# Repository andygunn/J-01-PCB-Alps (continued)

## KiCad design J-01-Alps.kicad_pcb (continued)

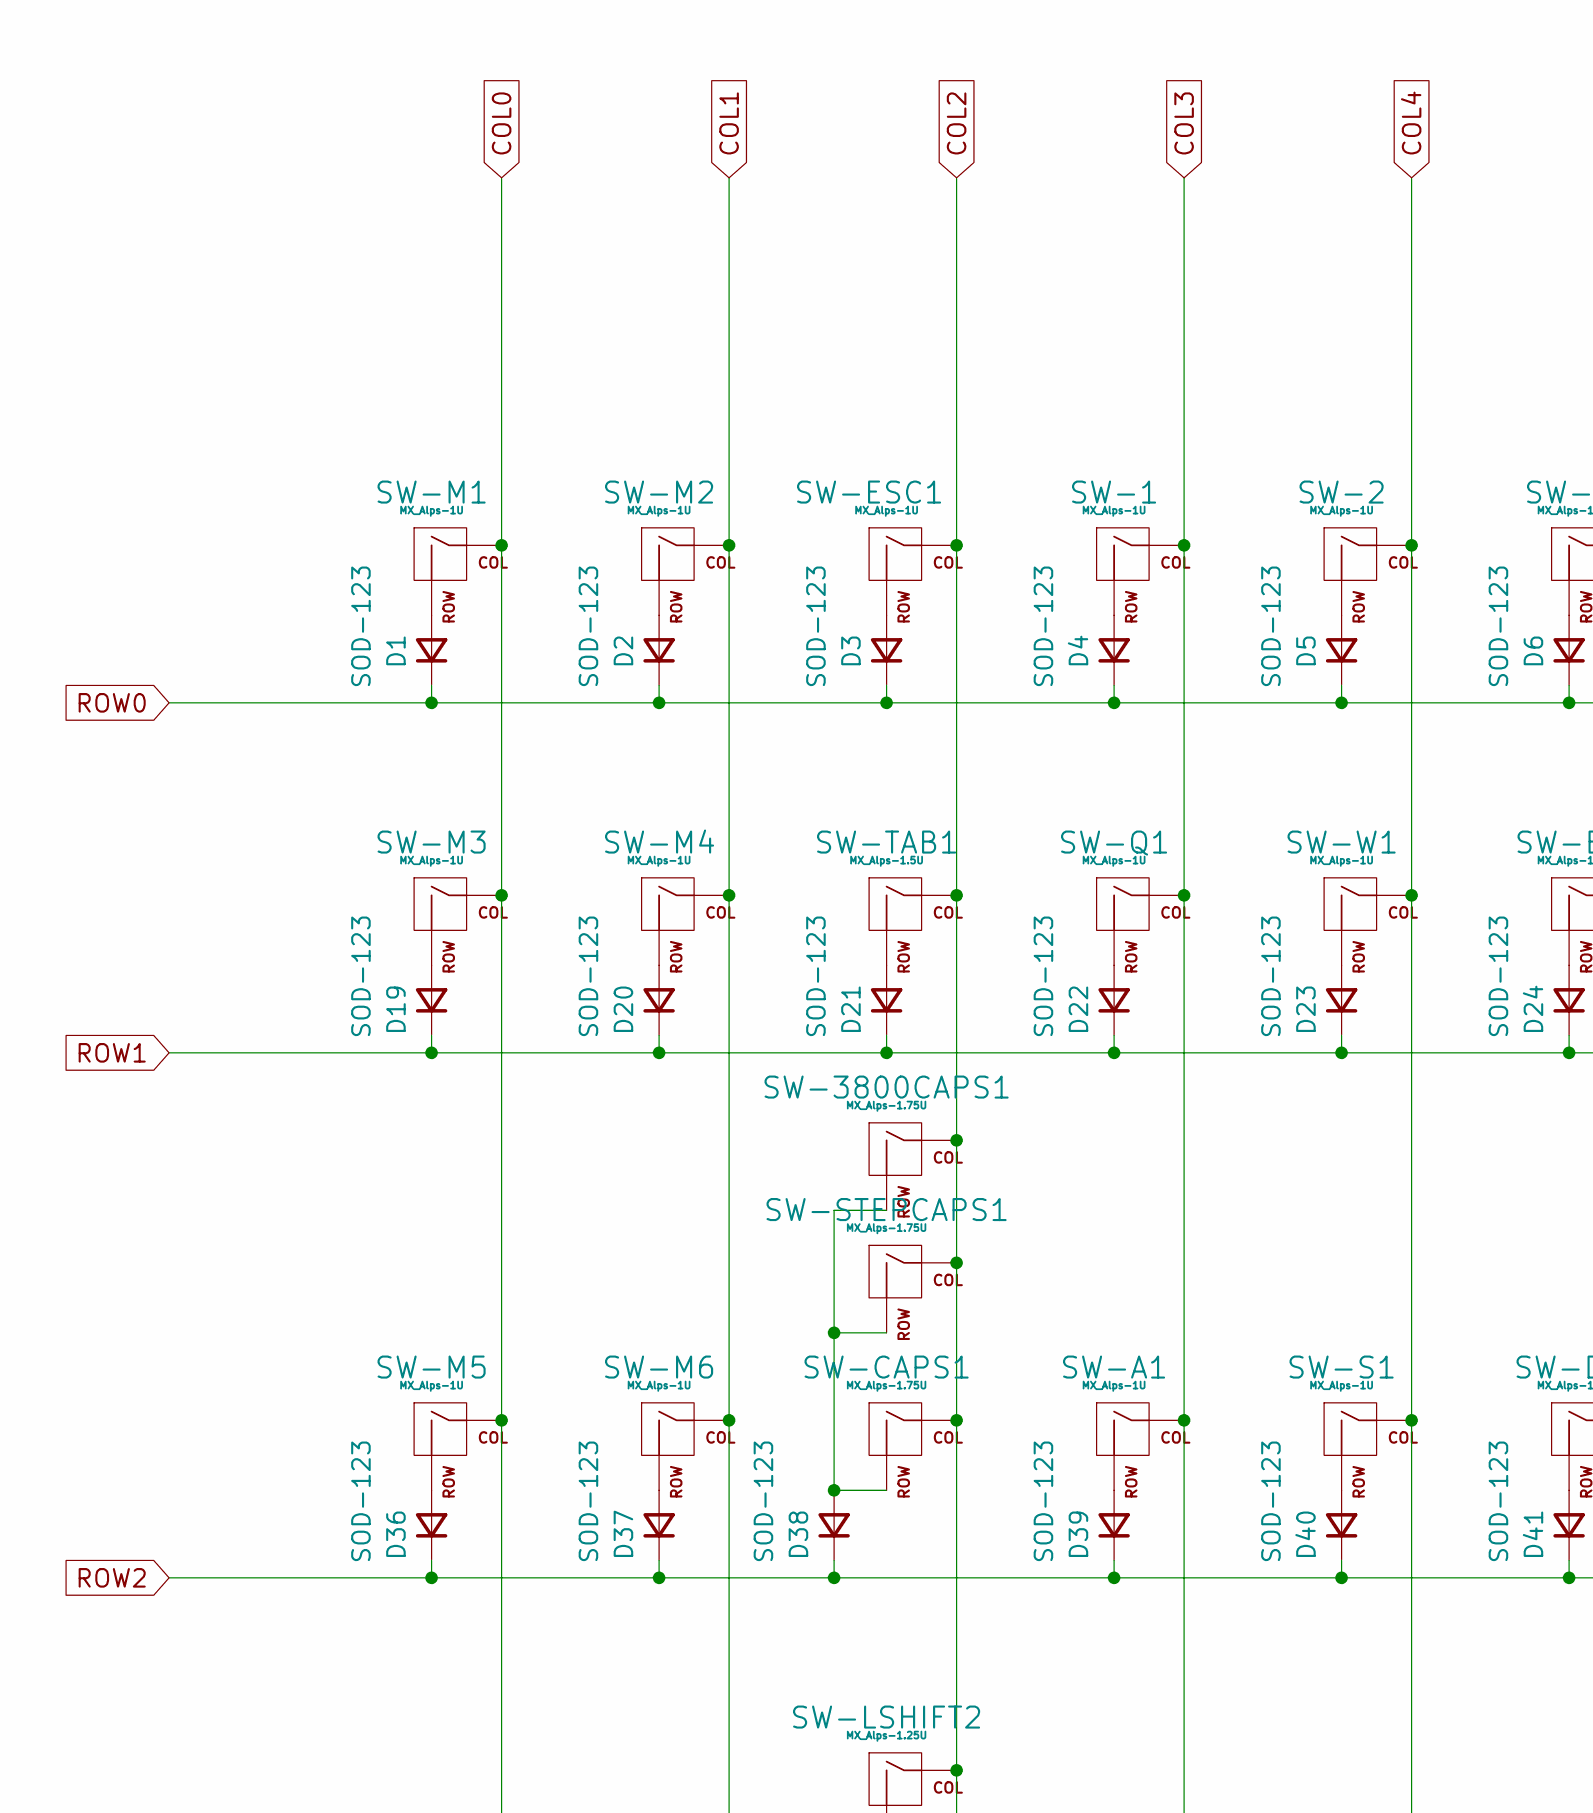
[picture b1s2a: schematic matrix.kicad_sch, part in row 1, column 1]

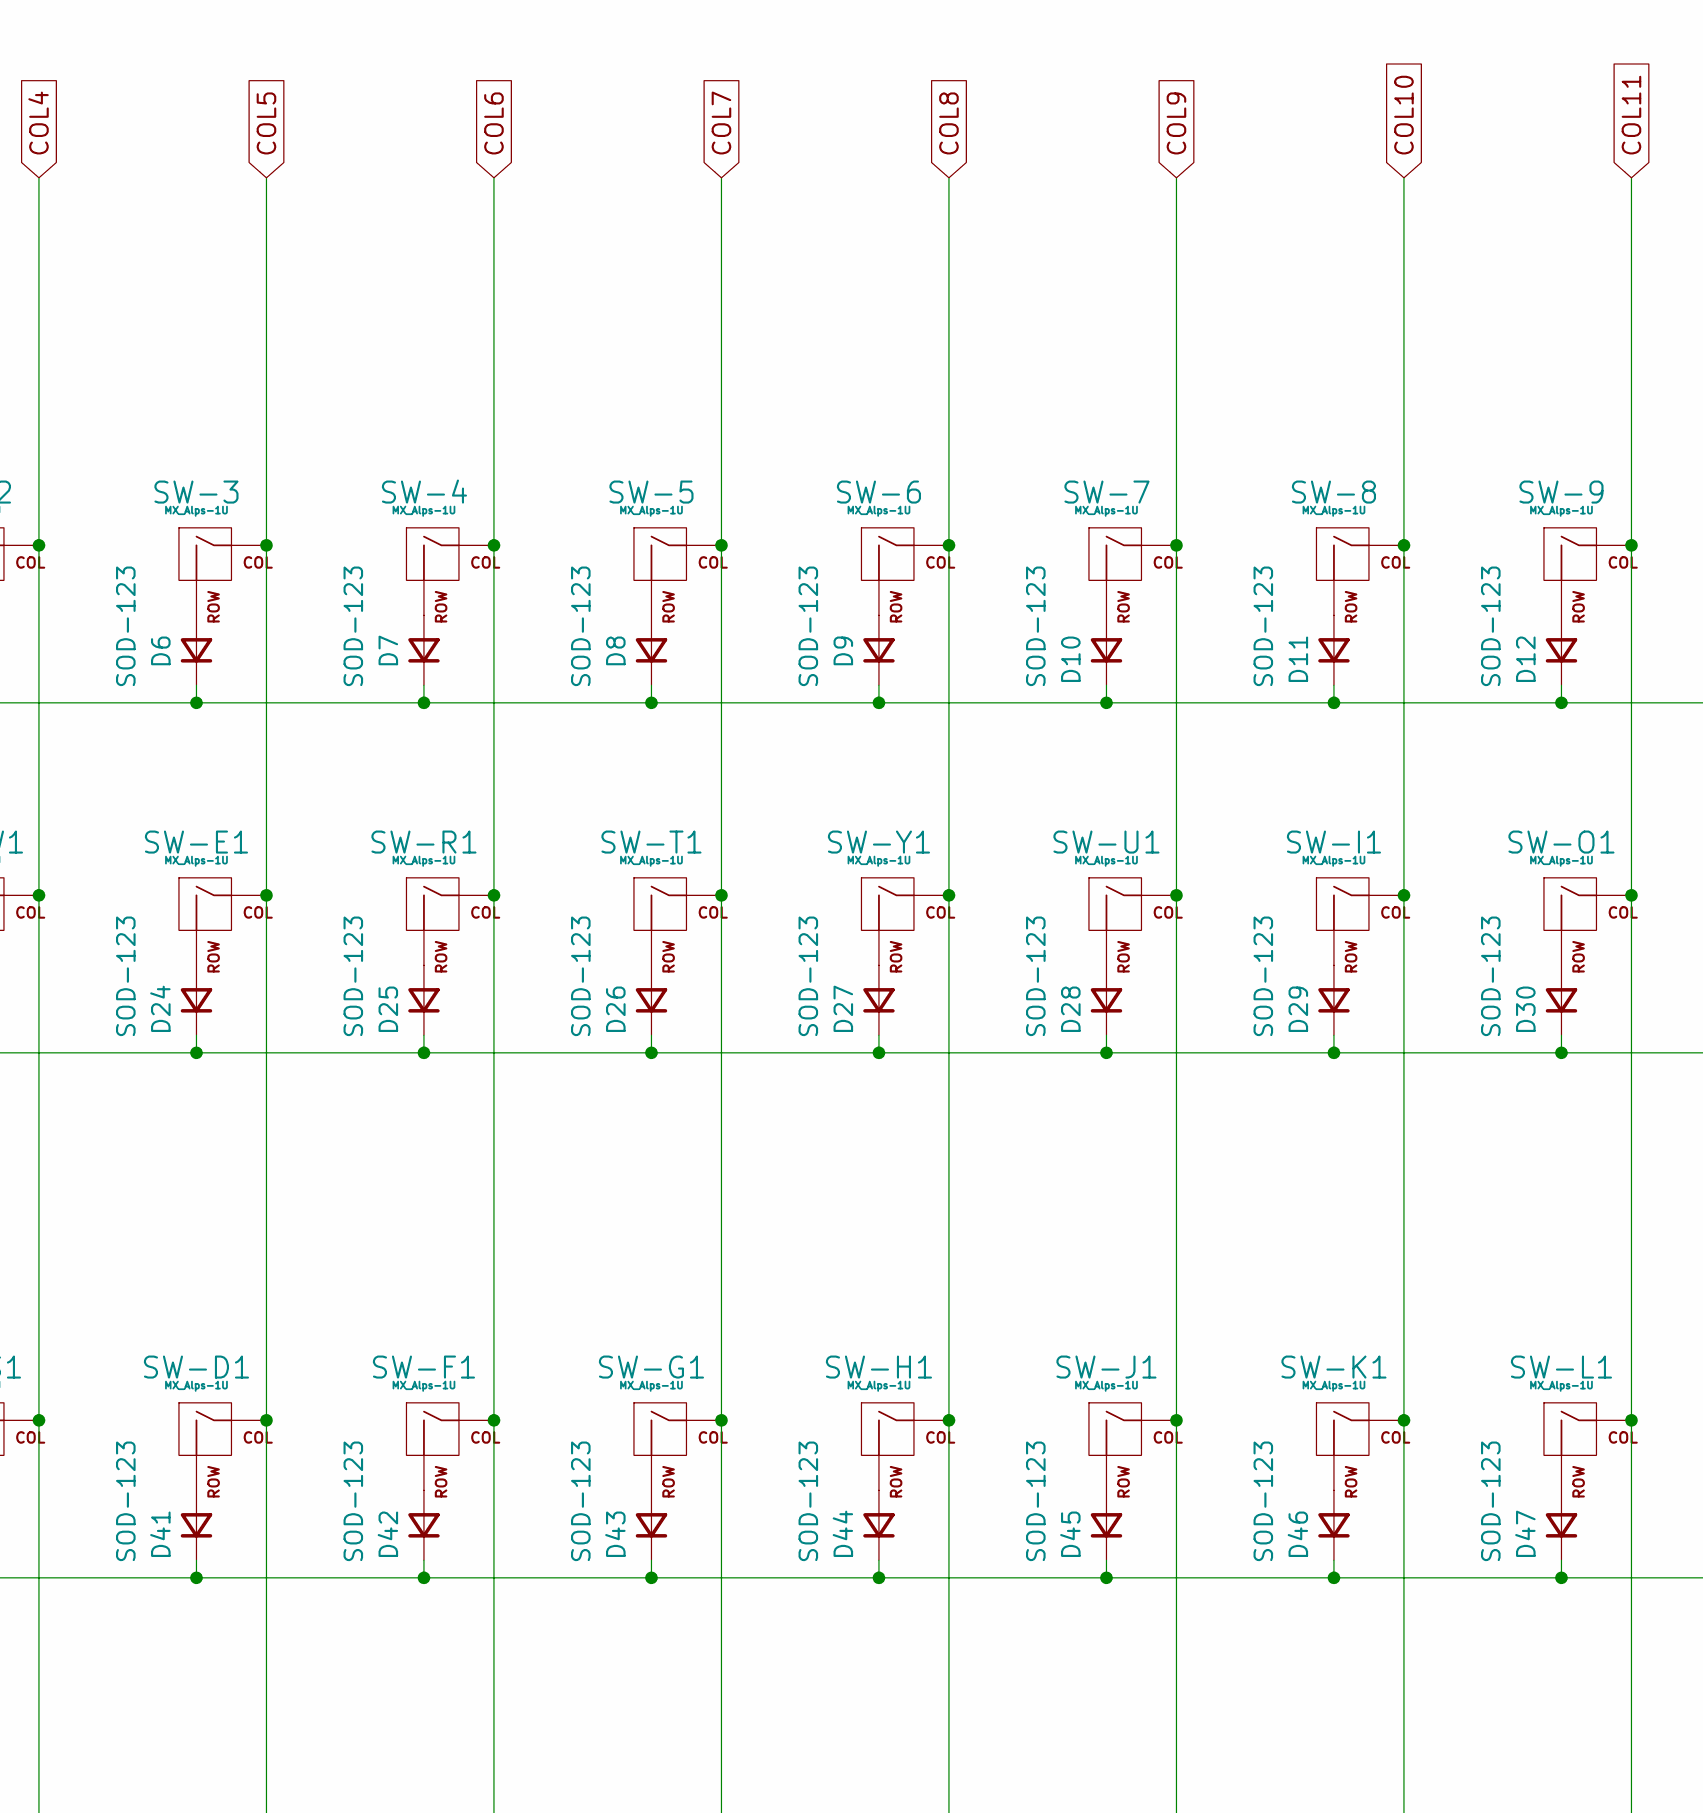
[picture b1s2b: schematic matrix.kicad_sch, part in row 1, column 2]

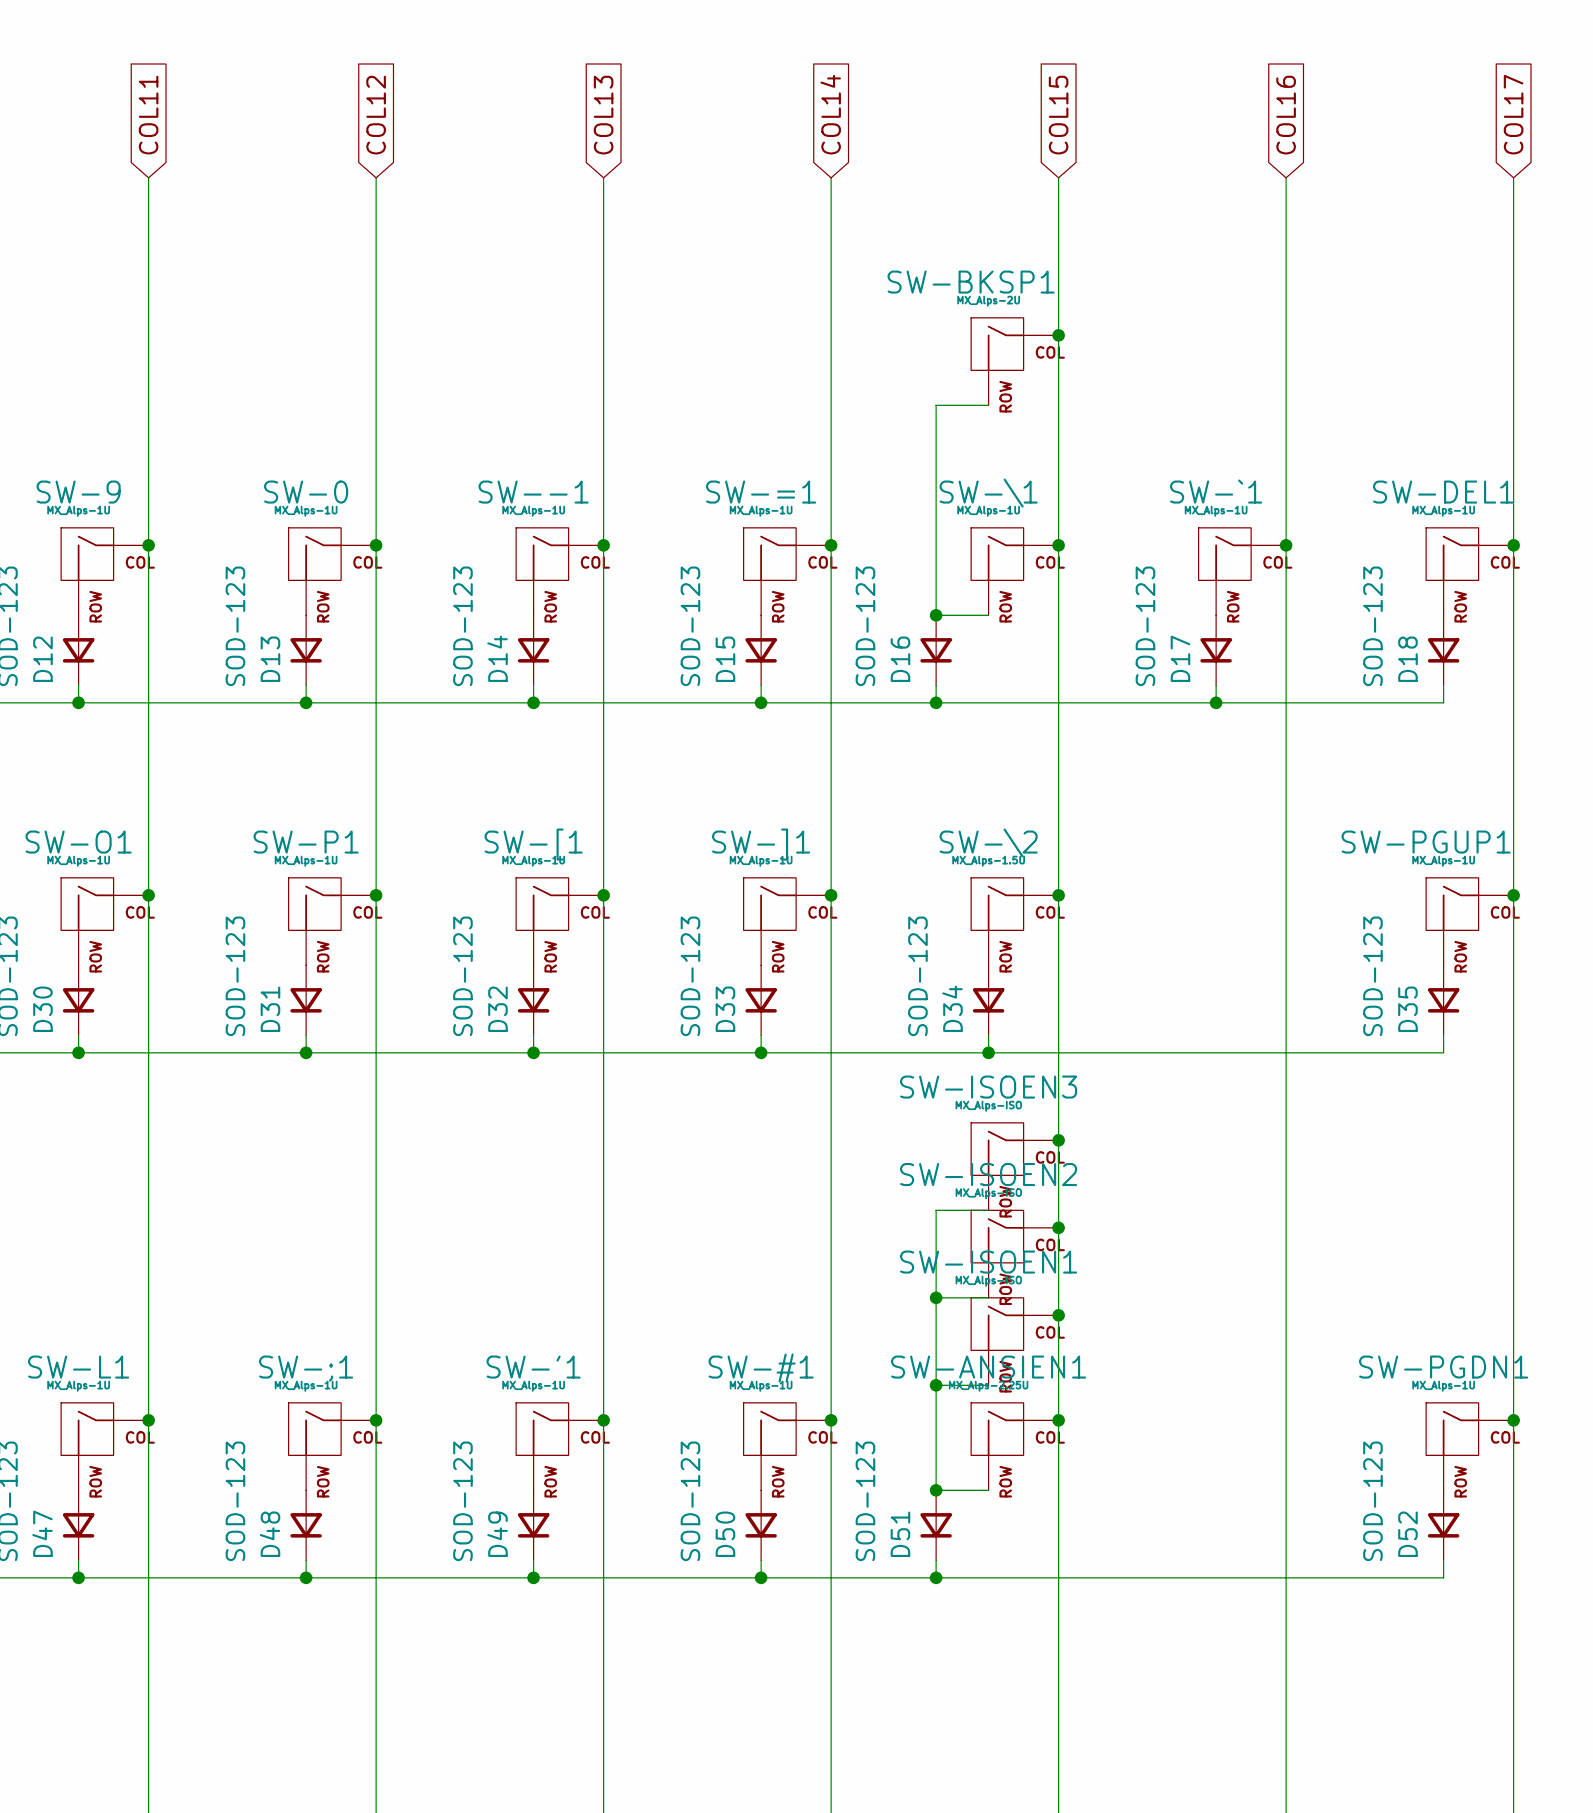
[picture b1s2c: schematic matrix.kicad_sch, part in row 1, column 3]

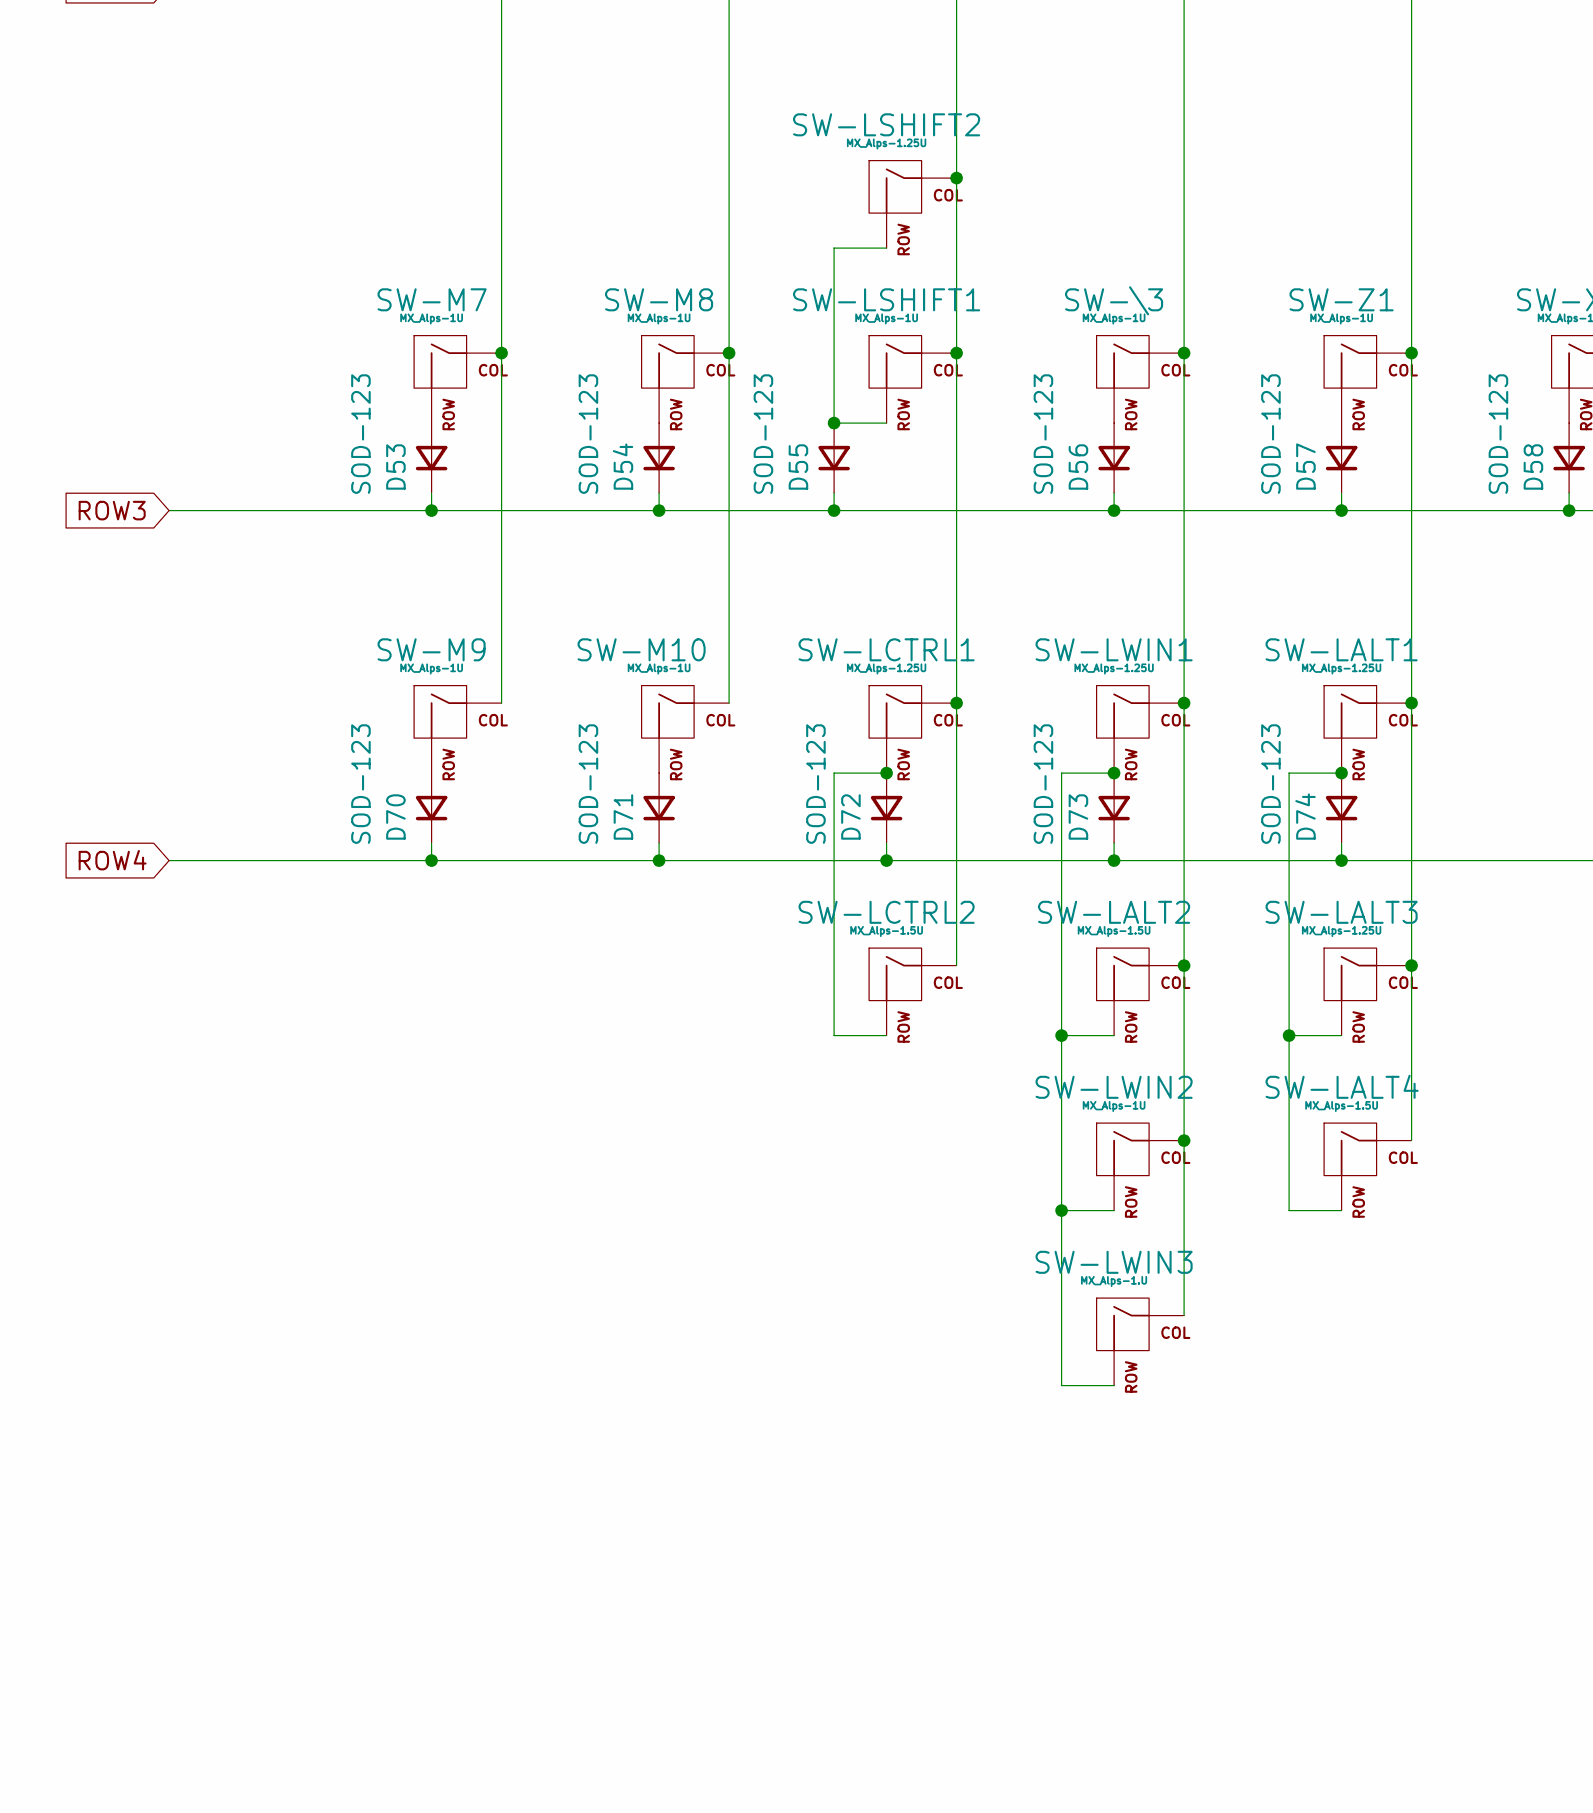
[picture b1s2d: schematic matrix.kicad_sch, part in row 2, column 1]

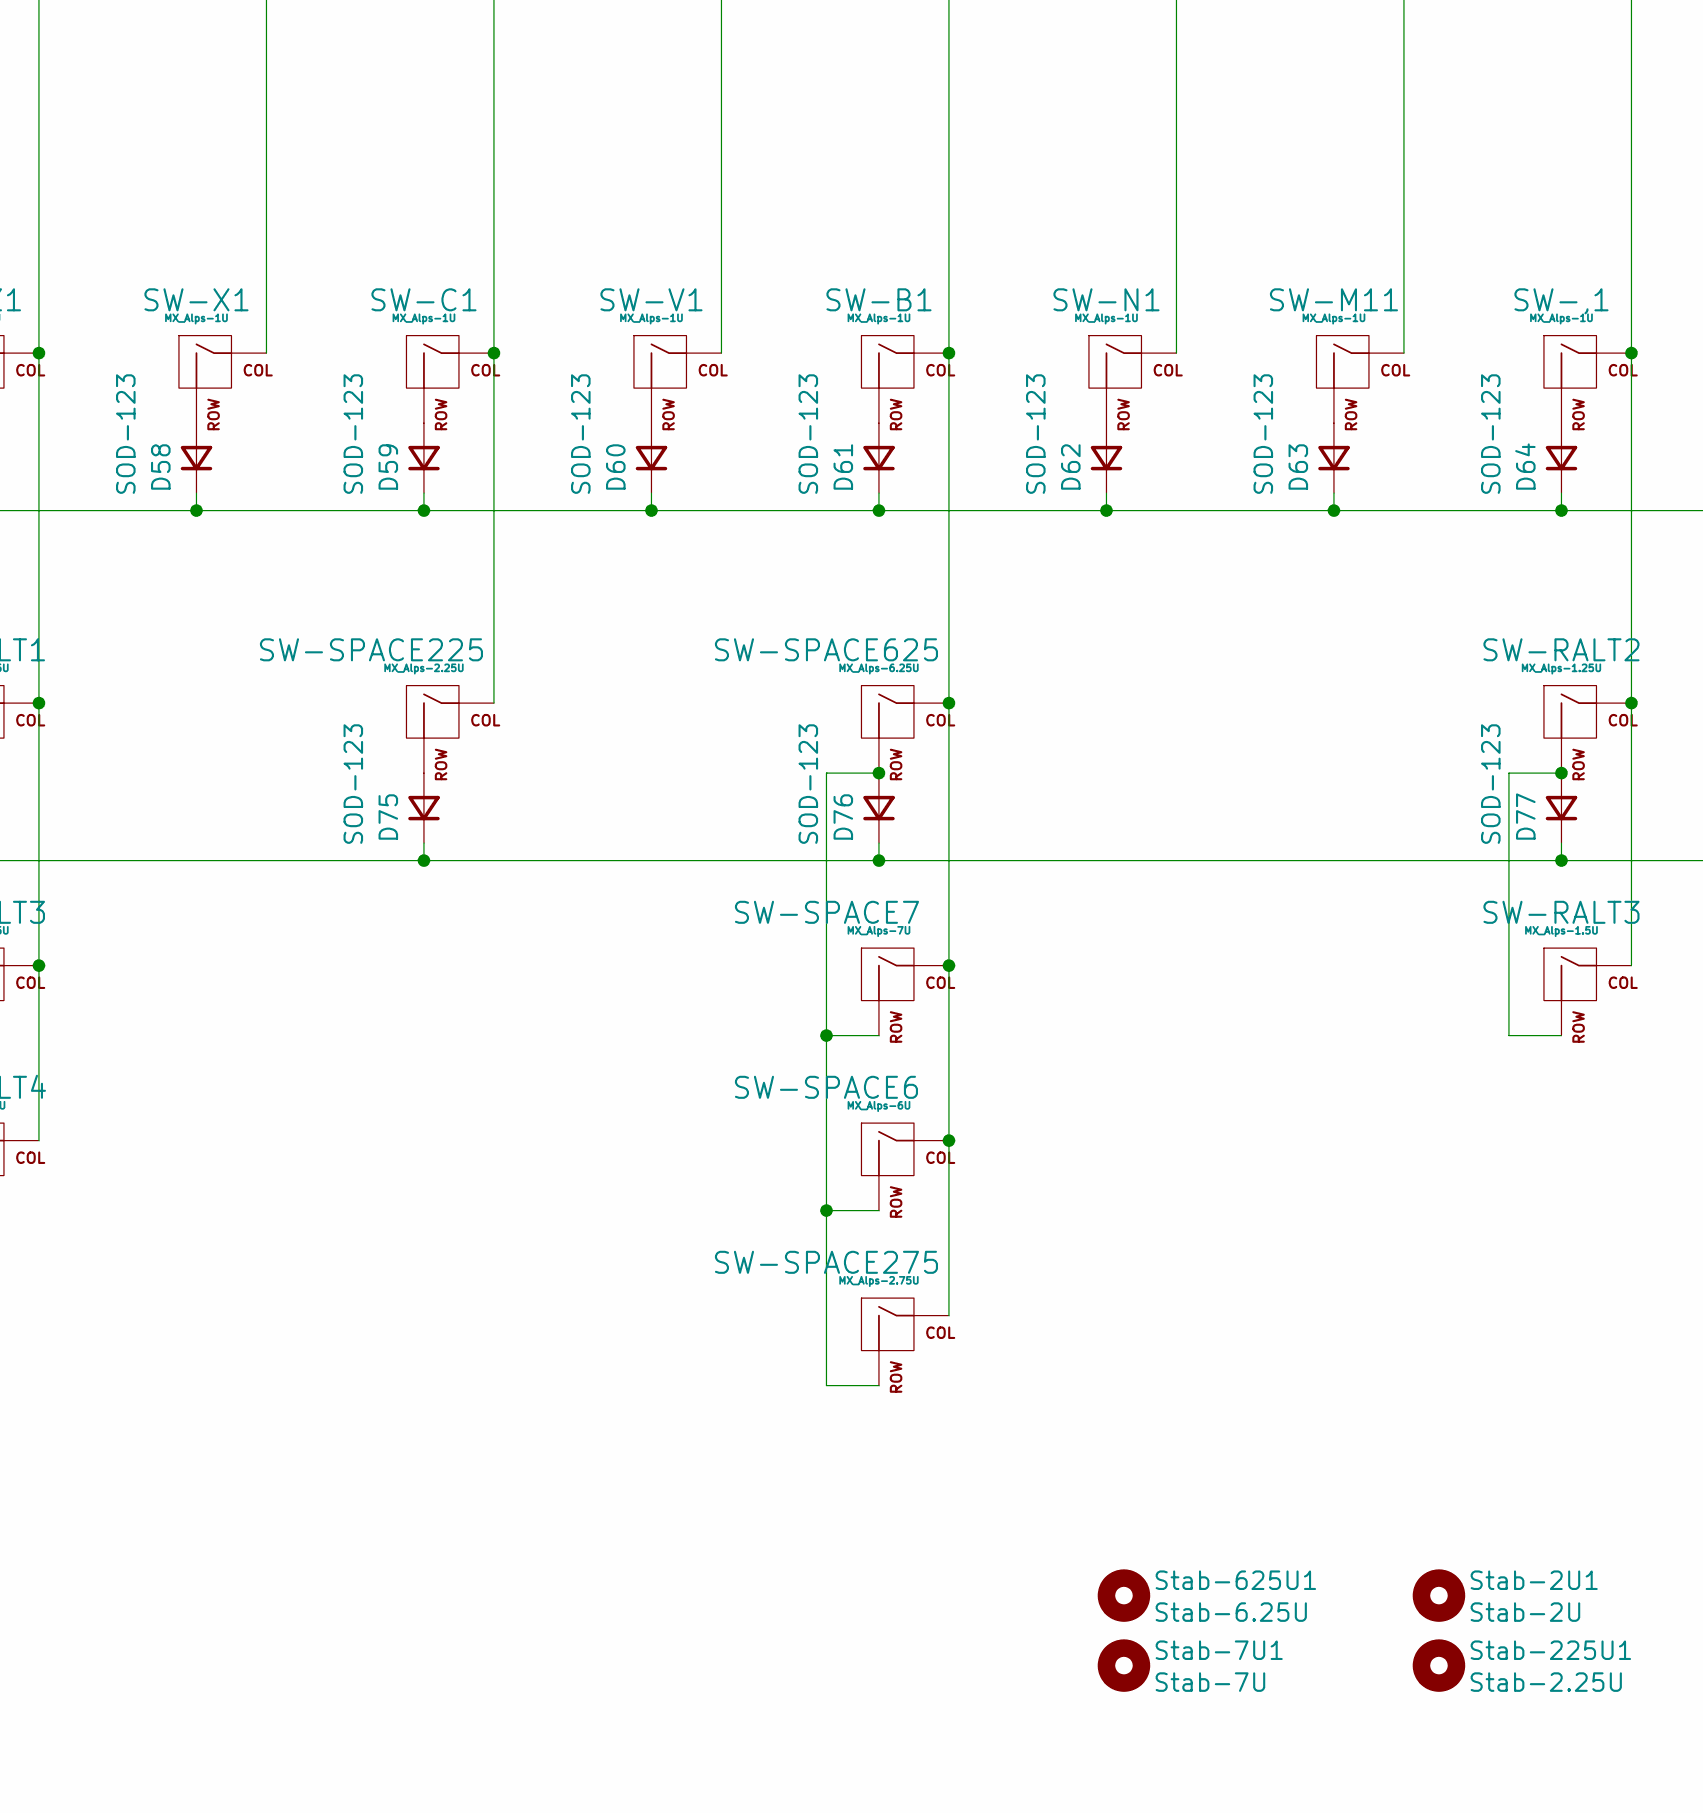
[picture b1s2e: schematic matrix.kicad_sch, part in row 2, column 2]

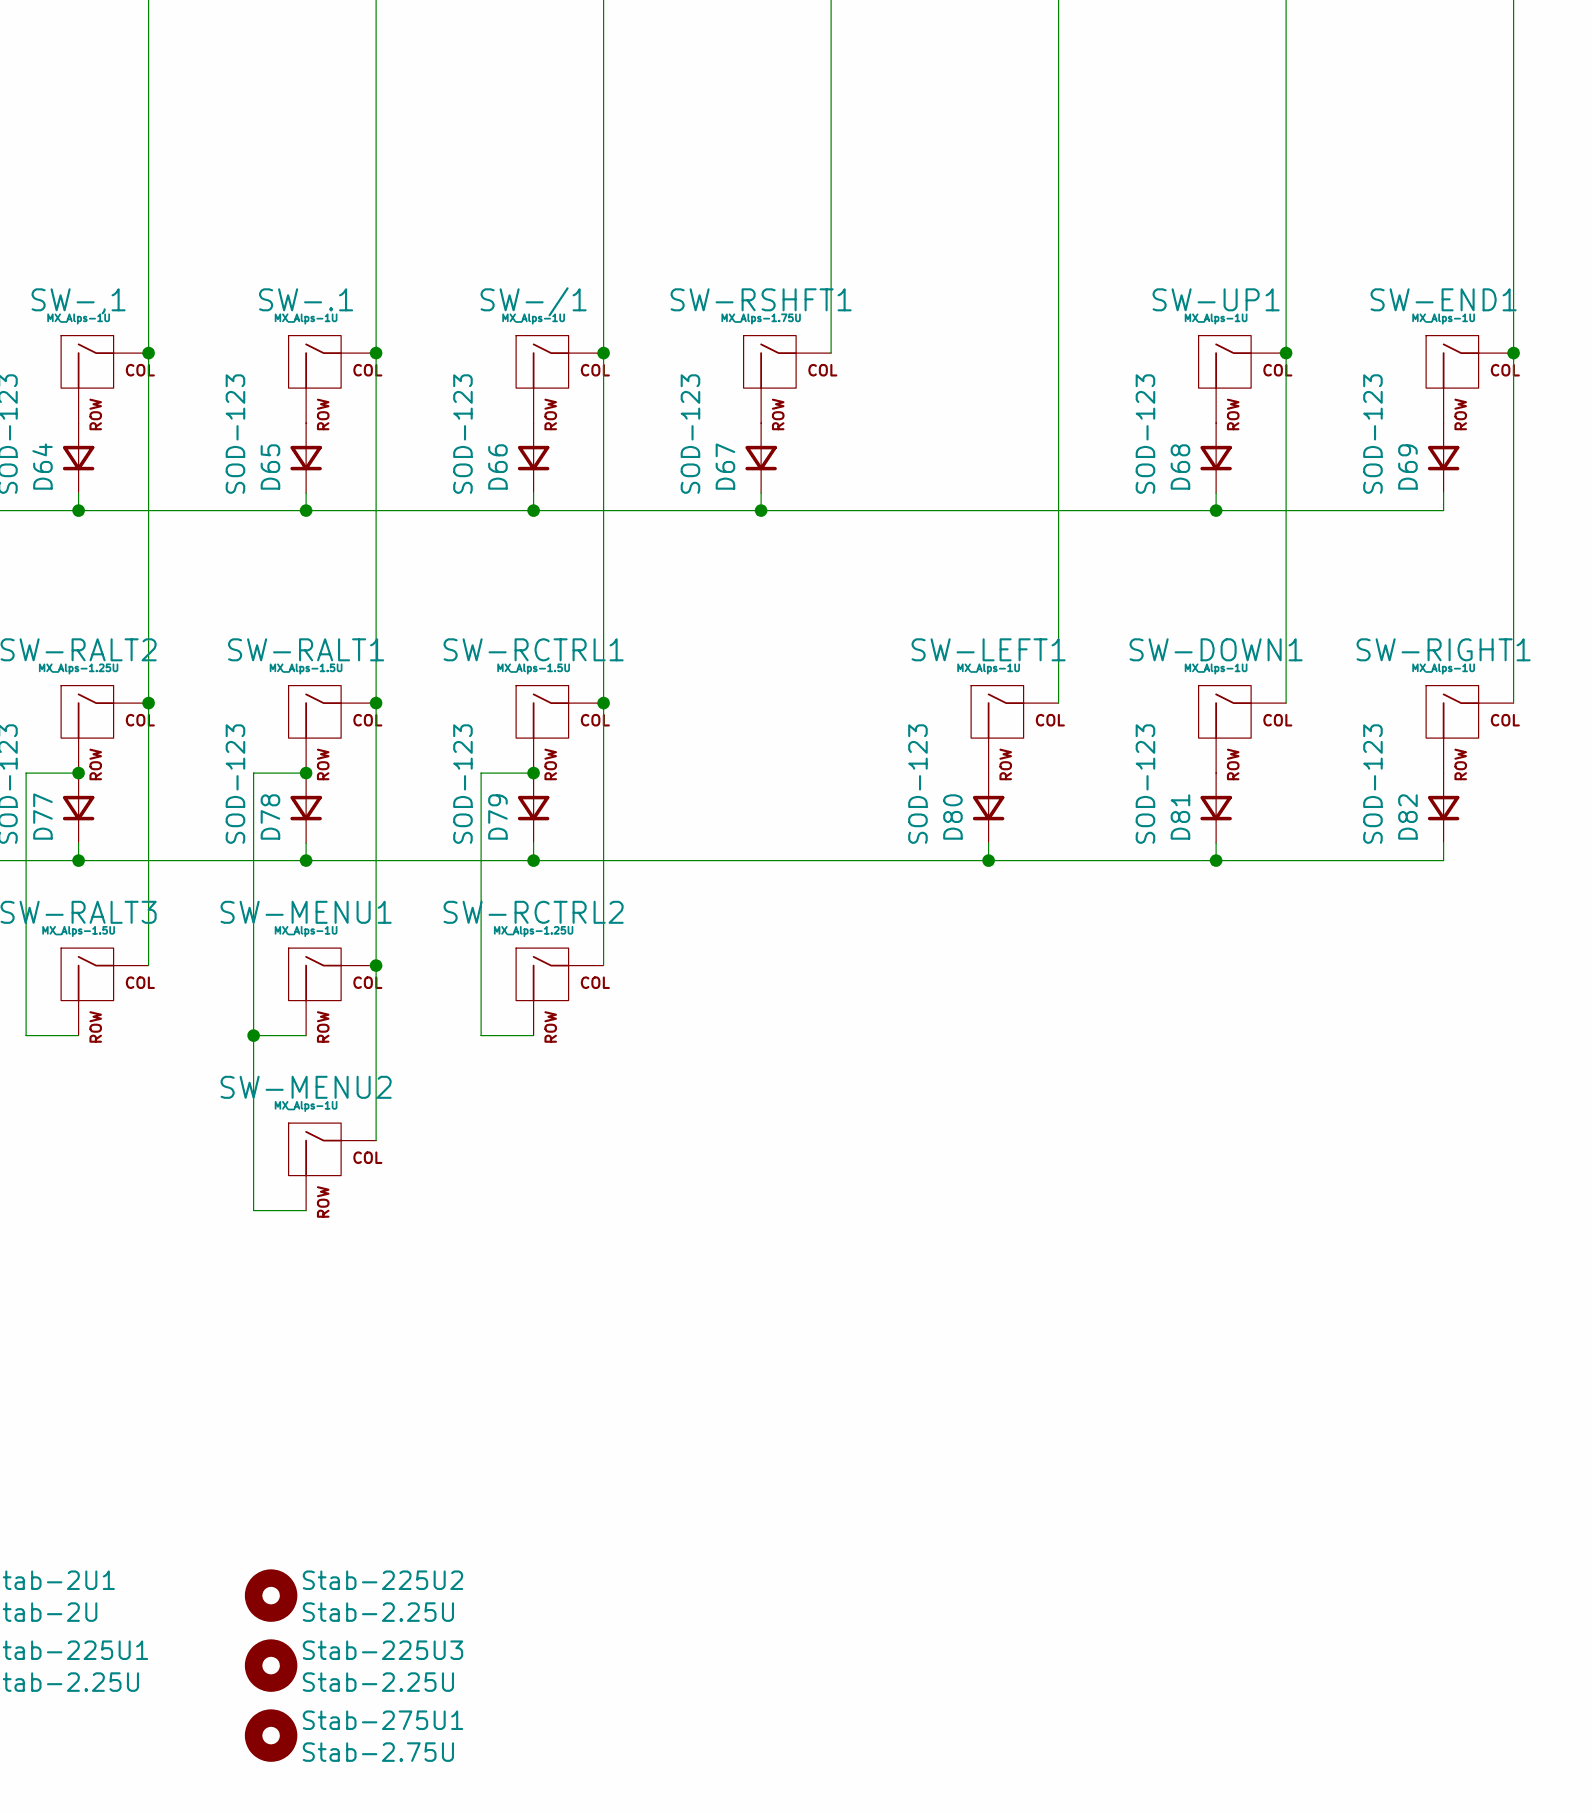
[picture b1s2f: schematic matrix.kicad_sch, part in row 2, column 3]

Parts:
D1, D2, D3, D4, D5, D6, D7, D8, D9, D10, D11, D12, D13, D14, D15, D16, D17, D18, D19, D20, D21, D22, D23, D24, D25, D26, D27, D28, D29, D30, D31, D32, D33, D34, D35, D36, D37, D38, D39, D40, D41, D42, D43, D44, D45, D46, D47, D48, D49, D50, D51, D52, D53, D54, D55, D56, D57, D58, D59, D60, D61, D62, D63, D64, D65, D66, D67, D68, D69, D70, D71, D72, D73, D74, D75, D76, D77, D78, D79, D80, D81, D82: SOD-123; D_SOD-123; LCSC C81598
SW-0, SW-1, SW-2, SW-3, SW-4, SW-5, SW-6, SW-7, SW-8, SW-9, SW-.1: MX_Alps-1U; ALPS-1U
SW-3800CAPS1: MX_Alps-1.75U; ALPS-1.5U
SW-#1: MX_Alps-1U; ALPS-1U
SW-'1: MX_Alps-1U; ALPS-1U
SW-,1: MX_Alps-1U; ALPS-1U
SW--1: MX_Alps-1U; ALPS-1U
SW-/1: MX_Alps-1U; ALPS-1U
SW-;1: MX_Alps-1U; ALPS-1U
SW-=1: MX_Alps-1U; ALPS-1U
SW-A1: MX_Alps-1U; ALPS-1U
SW-ANSIEN1: MX_Alps-2.25U; ALPS-2.25U
SW-B1: MX_Alps-1U; ALPS-1U
SW-BKSP1: MX_Alps-2U; ALPS-2U
SW-C1: MX_Alps-1U; ALPS-1U
SW-CAPS1: MX_Alps-1.75U; ALPS-1.75U
SW-D1: MX_Alps-1U; ALPS-1U
SW-DEL1: MX_Alps-1U; ALPS-1U
SW-DOWN1: MX_Alps-1U; ALPS-1U
SW-E1: MX_Alps-1U; ALPS-1U
SW-END1: MX_Alps-1U; ALPS-1U
SW-ESC1: MX_Alps-1U; ALPS-1U
SW-F1: MX_Alps-1U; ALPS-1U
SW-G1: MX_Alps-1U; ALPS-1U
SW-H1: MX_Alps-1U; ALPS-1U
SW-I1: MX_Alps-1U; ALPS-1U
SW-ISOEN1: MX_Alps-ISO; ALPS-ISO-FLIPPED
SW-ISOEN2, SW-ISOEN3: MX_Alps-ISO; ALPS-1U
SW-J1: MX_Alps-1U; ALPS-1U
SW-K1: MX_Alps-1U; ALPS-1U
SW-L1: MX_Alps-1U; ALPS-1U
SW-LALT1, SW-LALT3: MX_Alps-1.25U; ALPS-1.25U
SW-LALT2, SW-LALT4: MX_Alps-1.5U; ALPS-1.5U
SW-LCTRL1: MX_Alps-1.25U; ALPS-1.25U
SW-LCTRL2: MX_Alps-1.5U; ALPS-1.5U
SW-LEFT1: MX_Alps-1U; ALPS-1U
SW-LSHIFT1: MX_Alps-1U; ALPS-2.25U
SW-LSHIFT2: MX_Alps-1.25U; ALPS-1.25U
SW-LWIN1: MX_Alps-1.25U; ALPS-1.25U
SW-LWIN2: MX_Alps-1U; ALPS-1U
SW-LWIN3: MX_Alps-1.U; ALPS-1U
SW-M1, SW-M2, SW-M3, SW-M4, SW-M5, SW-M6, SW-M7, SW-M8, SW-M9, SW-M10, SW-M11: MX_Alps-1U; ALPS-1U
SW-MENU1, SW-MENU2: MX_Alps-1U; ALPS-1U
SW-N1: MX_Alps-1U; ALPS-1U
SW-O1: MX_Alps-1U; ALPS-1U
SW-P1: MX_Alps-1U; ALPS-1U
SW-PGDN1: MX_Alps-1U; ALPS-1U
SW-PGUP1: MX_Alps-1U; ALPS-1U
SW-Q1: MX_Alps-1U; ALPS-1U
SW-R1: MX_Alps-1U; ALPS-1U
SW-RALT1, SW-RALT3: MX_Alps-1.5U; ALPS-1.5U
SW-RALT2: MX_Alps-1.25U; ALPS-1.25U
SW-RCTRL1: MX_Alps-1.5U; ALPS-1.5U
SW-RCTRL2: MX_Alps-1.25U; ALPS-1.25U
SW-RIGHT1: MX_Alps-1U; ALPS-1U
SW-RSHFT1: MX_Alps-1.75U; ALPS-1.75U
SW-S1: MX_Alps-1U; ALPS-1U
SW-SPACE6: MX_Alps-6U; MX-6U-Centered-ReversedStabilizers-NoLED
SW-SPACE7: MX_Alps-7U; ALPS-7U
SW-SPACE225: MX_Alps-2.25U; ALPS-2.25U
SW-SPACE275: MX_Alps-2.75U; ALPS-2.75U
SW-SPACE625: MX_Alps-6.25U; ALPS-6.25U
SW-STEPCAPS1: MX_Alps-1.75U; ALPS-1.25U
SW-T1: MX_Alps-1U; ALPS-1U
SW-TAB1: MX_Alps-1.5U; ALPS-1.5U
SW-U1: MX_Alps-1U; ALPS-1U
SW-UP1: MX_Alps-1U; ALPS-1U
SW-V1: MX_Alps-1U; ALPS-1U
SW-W1: MX_Alps-1U; ALPS-1U
SW-X1: MX_Alps-1U; ALPS-1U
SW-Y1: MX_Alps-1U; ALPS-1U
SW-Z1: MX_Alps-1U; ALPS-1U
SW-[1: MX_Alps-1U; ALPS-1U
SW-\1, SW-\3: MX_Alps-1U; ALPS-1U
SW-\2: MX_Alps-1.5U; ALPS-1.5U
SW-]1: MX_Alps-1U; ALPS-1U
SW-`1: MX_Alps-1U; ALPS-1U
Stab-2U1: Stab-2U; MX-2U-Stab-Only
Stab-7U1: Stab-7U; MX-7U-Stab-Only-Reversed
Stab-225U1, Stab-225U2, Stab-225U3: Stab-2.25U; MX-2.25U-Stab-Only
Stab-275U1: Stab-2.75U; MX-2.75U-Stab-Only
Stab-625U1: Stab-6.25U; MX-6.25U-Stab-Only-Reversed

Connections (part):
COL0: SW-M1.1 (COL), SW-M3.1 (COL), SW-M5.1 (COL), SW-M7.1 (COL), SW-M9.1 (COL); also elsewhere on the board
COL1: SW-M2.1 (COL), SW-M4.1 (COL), SW-M6.1 (COL), SW-M8.1 (COL), SW-M10.1 (COL); also elsewhere on the board
COL2: SW-3800CAPS1.1 (COL), SW-CAPS1.1 (COL), SW-ESC1.1 (COL), SW-LCTRL1.1 (COL), SW-LCTRL2.1 (COL), SW-LSHIFT1.1 (COL), SW-LSHIFT2.1 (COL), SW-STEPCAPS1.1 (COL), SW-TAB1.1 (COL); also elsewhere on the board
COL3: SW-1.1 (COL), SW-A1.1 (COL), SW-LALT2.1 (COL), SW-LWIN1.1 (COL), SW-LWIN2.1 (COL), SW-LWIN3.1 (COL), SW-Q1.1 (COL), SW-\3.1 (COL); also elsewhere on the board
COL4: SW-2.1 (COL), SW-LALT1.1 (COL), SW-LALT3.1 (COL), SW-LALT4.1 (COL), SW-S1.1 (COL), SW-W1.1 (COL), SW-Z1.1 (COL); also elsewhere on the board
COL5: SW-3.1 (COL), SW-D1.1 (COL), SW-E1.1 (COL), SW-X1.1 (COL); also elsewhere on the board
COL6: SW-4.1 (COL), SW-C1.1 (COL), SW-F1.1 (COL), SW-R1.1 (COL), SW-SPACE225.1 (COL); also elsewhere on the board
COL7: SW-5.1 (COL), SW-G1.1 (COL), SW-T1.1 (COL), SW-V1.1 (COL); also elsewhere on the board
COL8: SW-6.1 (COL), SW-B1.1 (COL), SW-H1.1 (COL), SW-SPACE6.1 (COL), SW-SPACE7.1 (COL), SW-SPACE275.1 (COL), SW-SPACE625.1 (COL), SW-Y1.1 (COL); also elsewhere on the board
COL9: SW-7.1 (COL), SW-J1.1 (COL), SW-N1.1 (COL), SW-U1.1 (COL); also elsewhere on the board
COL10: SW-8.1 (COL), SW-I1.1 (COL), SW-K1.1 (COL), SW-M11.1 (COL); also elsewhere on the board
COL11: SW-9.1 (COL), SW-,1.1 (COL), SW-L1.1 (COL), SW-O1.1 (COL), SW-RALT2.1 (COL), SW-RALT3.1 (COL); also elsewhere on the board
COL12: SW-0.1 (COL), SW-.1.1 (COL), SW-;1.1 (COL), SW-MENU1.1 (COL), SW-MENU2.1 (COL), SW-P1.1 (COL), SW-RALT1.1 (COL); also elsewhere on the board
COL13: SW-'1.1 (COL), SW--1.1 (COL), SW-/1.1 (COL), SW-RCTRL1.1 (COL), SW-RCTRL2.1 (COL), SW-[1.1 (COL); also elsewhere on the board
COL14: SW-#1.1 (COL), SW-=1.1 (COL), SW-RSHFT1.1 (COL), SW-]1.1 (COL); also elsewhere on the board
COL15: SW-ANSIEN1.1 (COL), SW-BKSP1.1 (COL), SW-ISOEN1.1 (COL), SW-ISOEN2.1 (COL), SW-ISOEN3.1 (COL), SW-LEFT1.1 (COL), SW-\1.1 (COL), SW-\2.1 (COL); also elsewhere on the board
COL16: SW-DOWN1.1 (COL), SW-UP1.1 (COL), SW-`1.1 (COL); also elsewhere on the board
COL17: SW-DEL1.1 (COL), SW-END1.1 (COL), SW-PGDN1.1 (COL), SW-PGUP1.1 (COL), SW-RIGHT1.1 (COL); also elsewhere on the board
unnamed: D1.2 (A), SW-M1.2 (ROW)
unnamed: D2.2 (A), SW-M2.2 (ROW)
unnamed: D3.2 (A), SW-ESC1.2 (ROW)
unnamed: D4.2 (A), SW-1.2 (ROW)
unnamed: D5.2 (A), SW-2.2 (ROW)
unnamed: D6.2 (A), SW-3.2 (ROW)
unnamed: D7.2 (A), SW-4.2 (ROW)
unnamed: D8.2 (A), SW-5.2 (ROW)
unnamed: D9.2 (A), SW-6.2 (ROW)
unnamed: D10.2 (A), SW-7.2 (ROW)
unnamed: D11.2 (A), SW-8.2 (ROW)
unnamed: D12.2 (A), SW-9.2 (ROW)
unnamed: D13.2 (A), SW-0.2 (ROW)
unnamed: D14.2 (A), SW--1.2 (ROW)
unnamed: D15.2 (A), SW-=1.2 (ROW)
unnamed: D16.2 (A), SW-BKSP1.2 (ROW), SW-\1.2 (ROW)
unnamed: D17.2 (A), SW-`1.2 (ROW)
unnamed: D18.2 (A), SW-DEL1.2 (ROW)
unnamed: D19.2 (A), SW-M3.2 (ROW)
unnamed: D20.2 (A), SW-M4.2 (ROW)
unnamed: D21.2 (A), SW-TAB1.2 (ROW)
unnamed: D22.2 (A), SW-Q1.2 (ROW)
unnamed: D23.2 (A), SW-W1.2 (ROW)
unnamed: D24.2 (A), SW-E1.2 (ROW)
unnamed: D25.2 (A), SW-R1.2 (ROW)
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
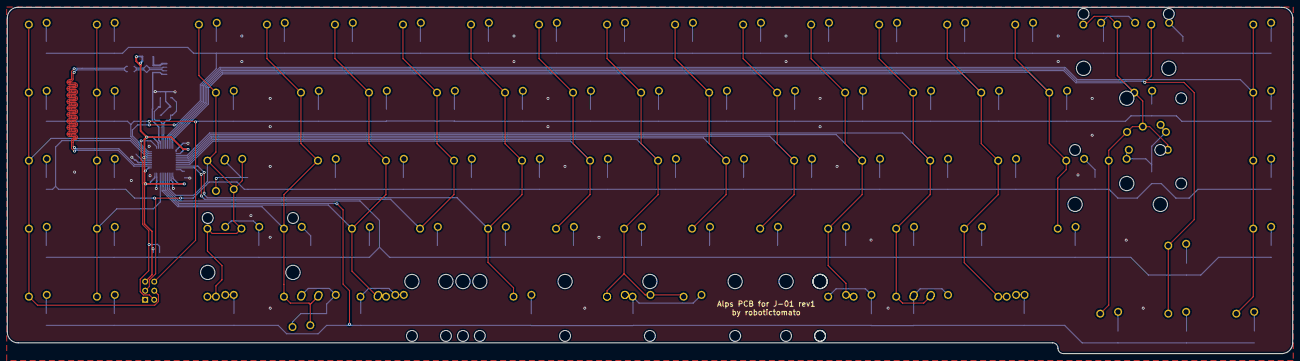
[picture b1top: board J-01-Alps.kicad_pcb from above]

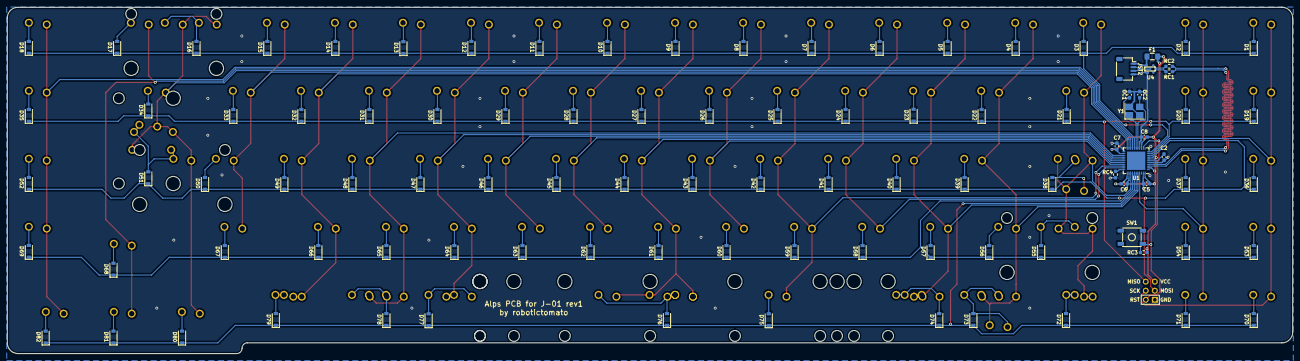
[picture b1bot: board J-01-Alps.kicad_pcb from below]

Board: 2 copper layers, 360.0 x 97.0 mm, 209 parts (100 on the bottom side), 117 nets.

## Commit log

2021-12-17 Adding submodules for libraries
2021-12-17 KiCad initialization
    Adding the library files to the KiCad project.
2021-12-17 Add JST library and start schematic
2021-12-17 Another attempt at adding more libraries
2021-12-19 MCU and Matrix Layout
    Continued work on the MCU component layout and the switch matrix.
2021-12-19 Matrix work
    Additional work on the switch matrix.
2021-12-19 Matrix Draft complete
    First draft of the switch matrix is complete.
2021-12-19 Bugfixes
2021-12-20 PCB layout started
    The beginning of the PCB layout - switch positions and two rows of diodes.
2021-12-22 Footprint changes
    Changed all of the MX+Alps footprints to Alps only. Also added MX Stabilizer footprints.
2021-12-23 Initial routing and additional switch footprints
    More bottom row option support (6U, split spacebar), and the start of some column and row routing.
2021-12-25 Routing work continued
    Most routes placed. Will need to be optimized and cleaned up, but most paths have been figured out.
2021-12-31 Continued work on layout
    Layout refinements, USB traces, etc.
2022-01-08 Verification of routing and dimension
    Finished verifying the routing is correct, and the edge-cut dimensions are correct. Double checked the separation between switch areas for Macro columns and arrows / 65% extension keys. Added renders.
2022-01-08 Generate Gerber, BOM, and POS files
    Generated production files, including Gerbers, BOM for JLCPCB, and positioning files (specific to JLCPCB).
2022-01-08 Add ZIP of BOM
    Added a Zip file to properly include the BOM and Positioning files.
2022-01-08 Modifications for QFN footprint
    Modifications for ATmega32U4-MU. Rerouting of USB traces, 5V lines, and other supporting components.
2022-01-09 Updated Gerber files
    Updated all production files for use at JLCPCB for manu.
2022-02-27 Cleanup
    A few small cleanup updates.
2022-02-27 Additional cleanup
    Move to Kicad 6 changes - archive old versions of files.
2022-02-27 Kicad 6 DRC cleanup
    Changes to the DRC tool for Kicad 6 required additional cleanup.
2022-02-28 Outline adjustment, footprint cleanup
2022-03-02 PCB dimension verification
    Double check of switch positions and edge dimensions.
2022-03-05 Trace cleanup and ISO Enter
    Continued trace cleanup for multi-position keys. Added support for three ISO enter orientations - 1.25 vertical and horizontal, and 1.5u vertical.
2022-03-06 Footprint cleanup, add AVR-ISP header footprint
    Some cleanup of the bottom row, ISO enter layout, and capslock footprints for more clearance. Addition of the AVR ISP header footprint and mapping to the MCU.
2022-03-06 Updated Gerber, BOM, and positioning files
    Final checkout of Gerbers, BOM, and positioning files.
2022-03-11 Created Zip file with BOM and Positioning files
2022-06-27 Content update - Gerber and plate files
    Added plate files directory and contents, removed excess Gerber files.
2022-12-24 Silkscreen and edge cut changes, update to .step files
    Modified the edge cut profile to be compatible with the upcoming rev2 release of the J-01. Changed silkscreen on front of PCB through-holes to prevent solder from flowing through. Updated Gerbers. Ch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
2022-12-26 Small change to footprint clearance
    There was a mistake in one of the footprint clearances. Fixed.
